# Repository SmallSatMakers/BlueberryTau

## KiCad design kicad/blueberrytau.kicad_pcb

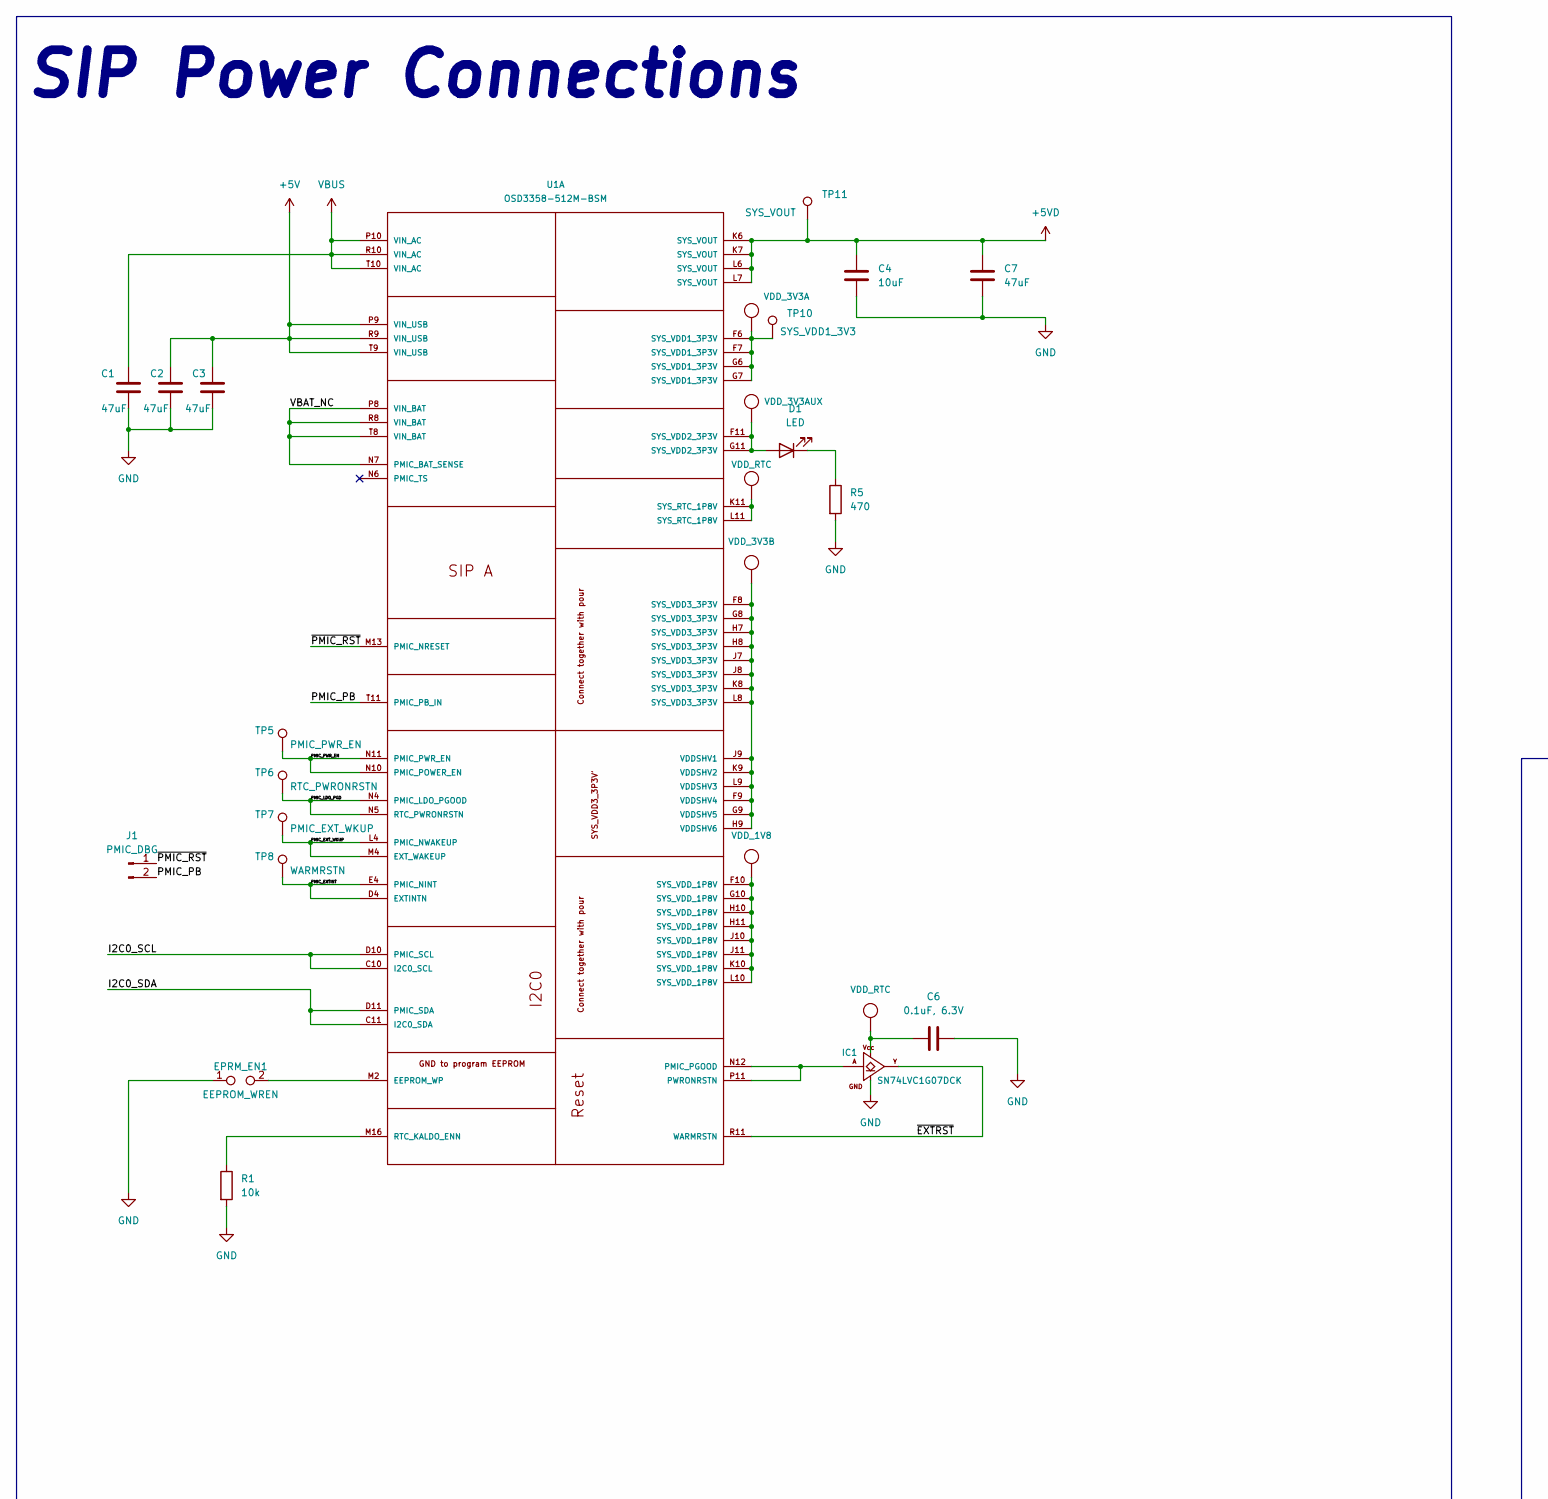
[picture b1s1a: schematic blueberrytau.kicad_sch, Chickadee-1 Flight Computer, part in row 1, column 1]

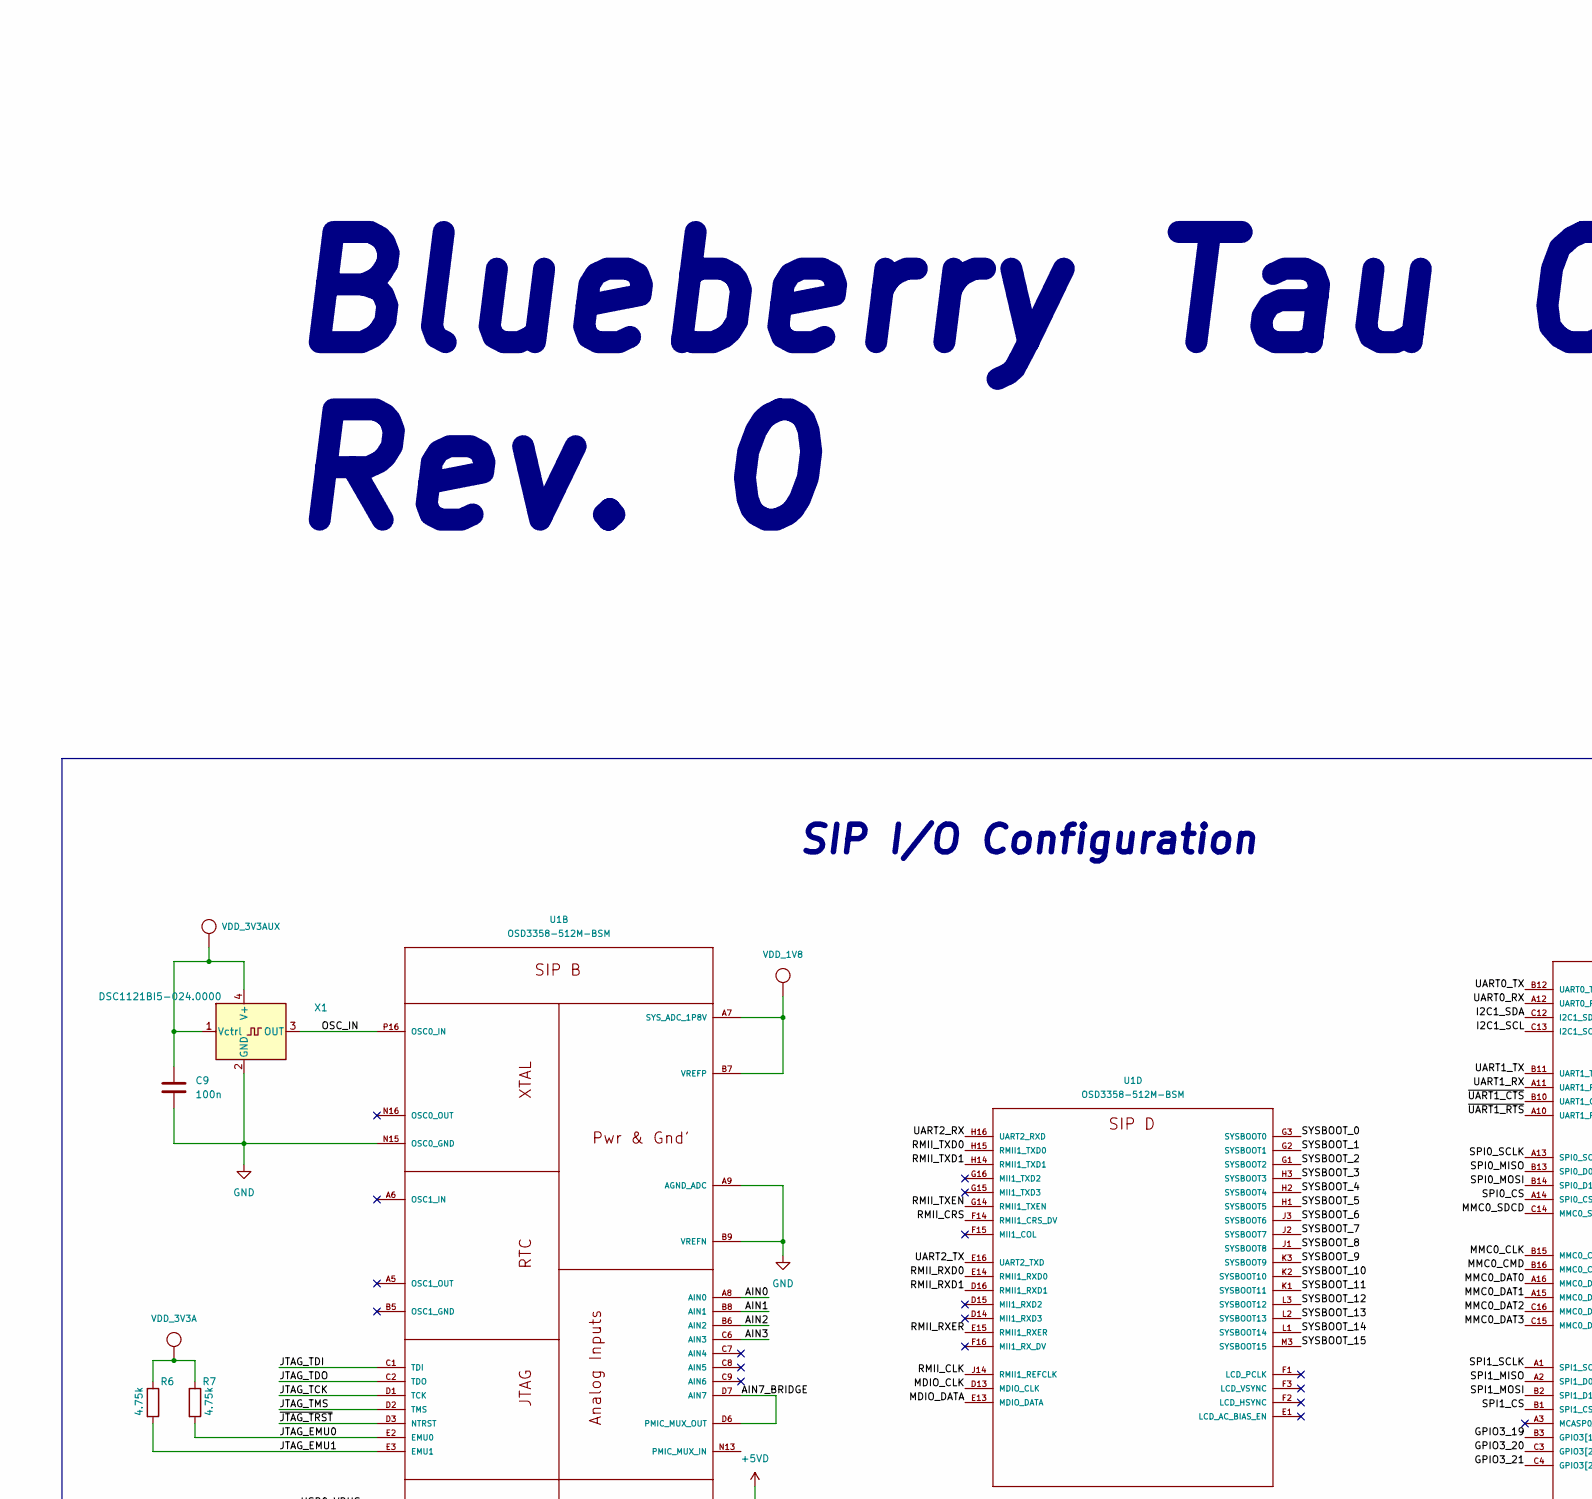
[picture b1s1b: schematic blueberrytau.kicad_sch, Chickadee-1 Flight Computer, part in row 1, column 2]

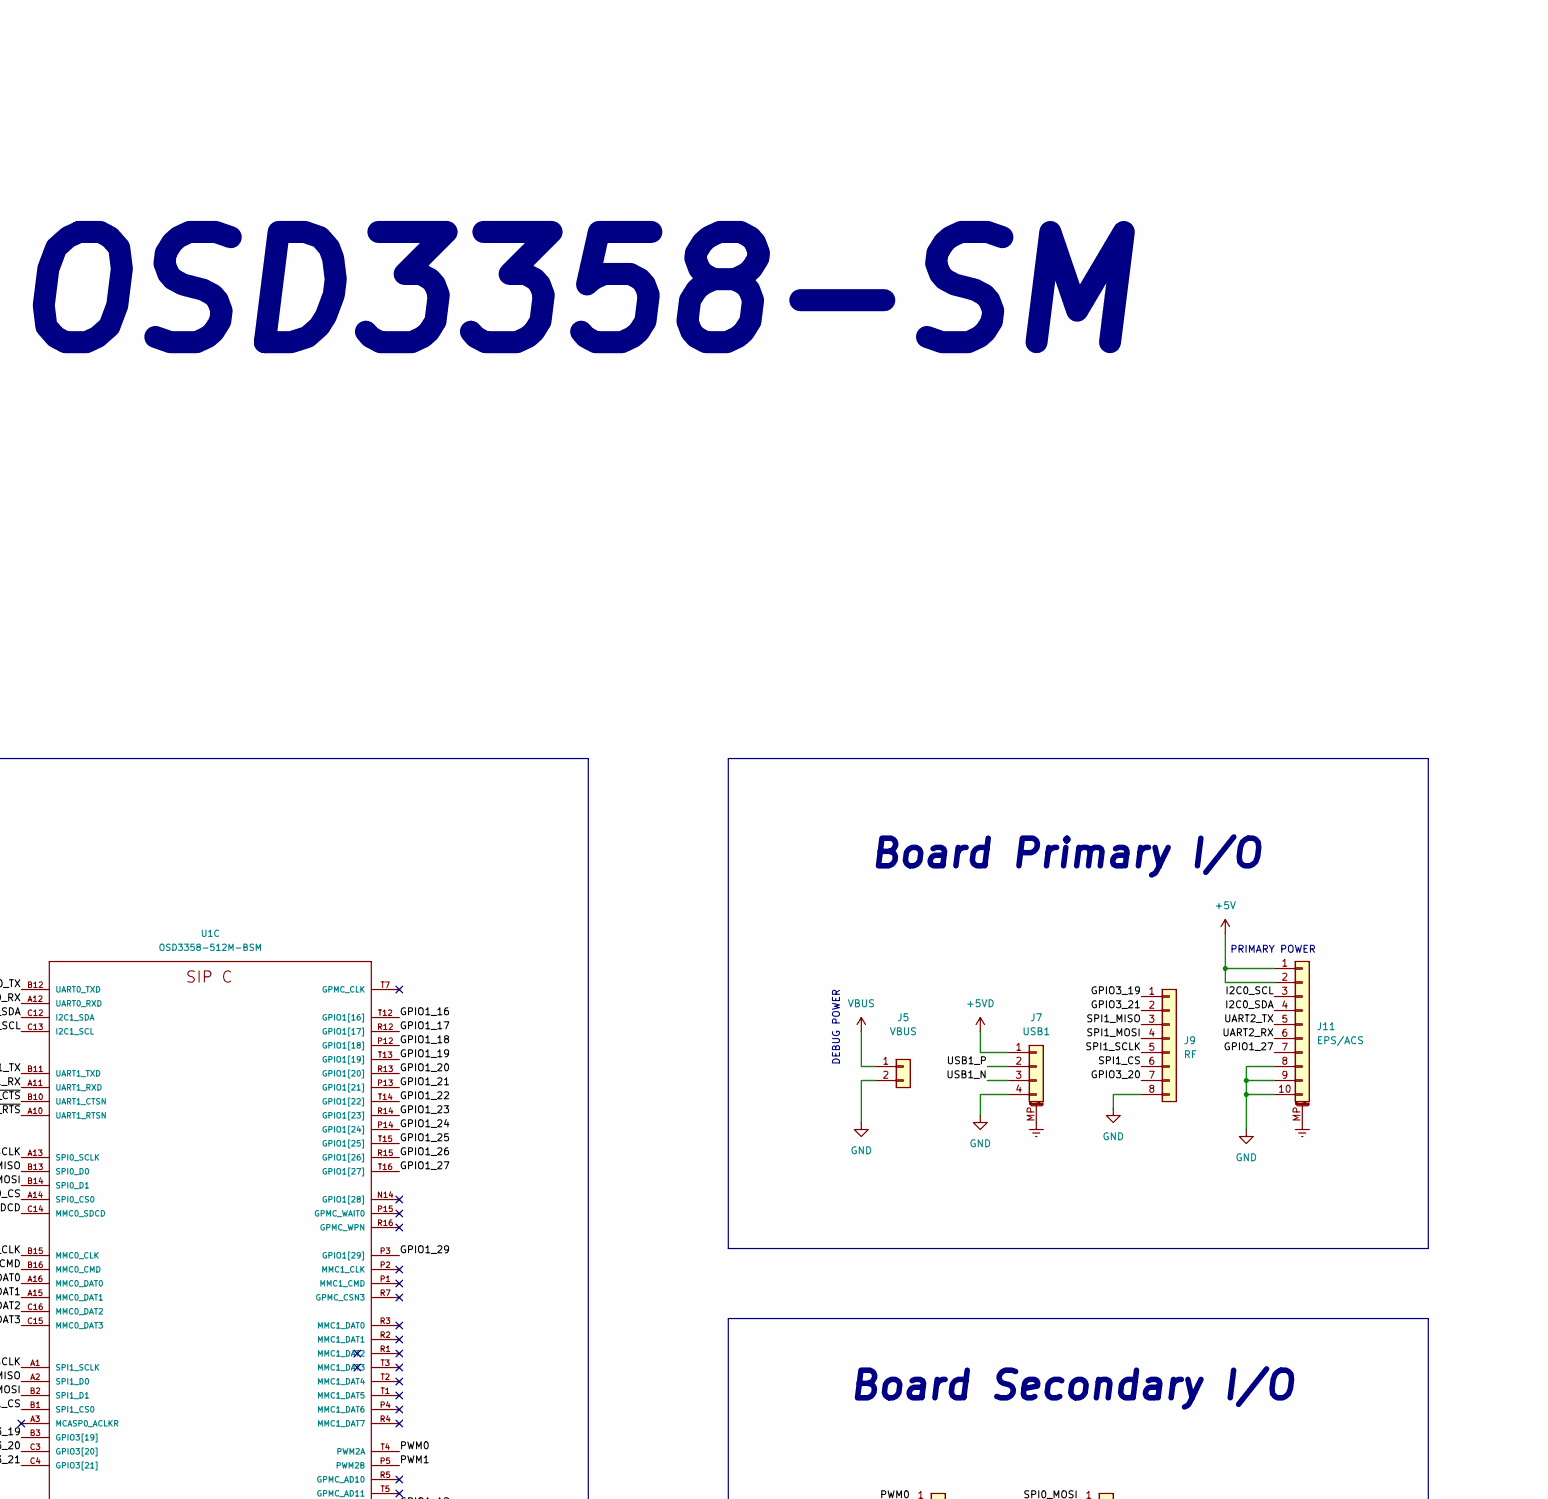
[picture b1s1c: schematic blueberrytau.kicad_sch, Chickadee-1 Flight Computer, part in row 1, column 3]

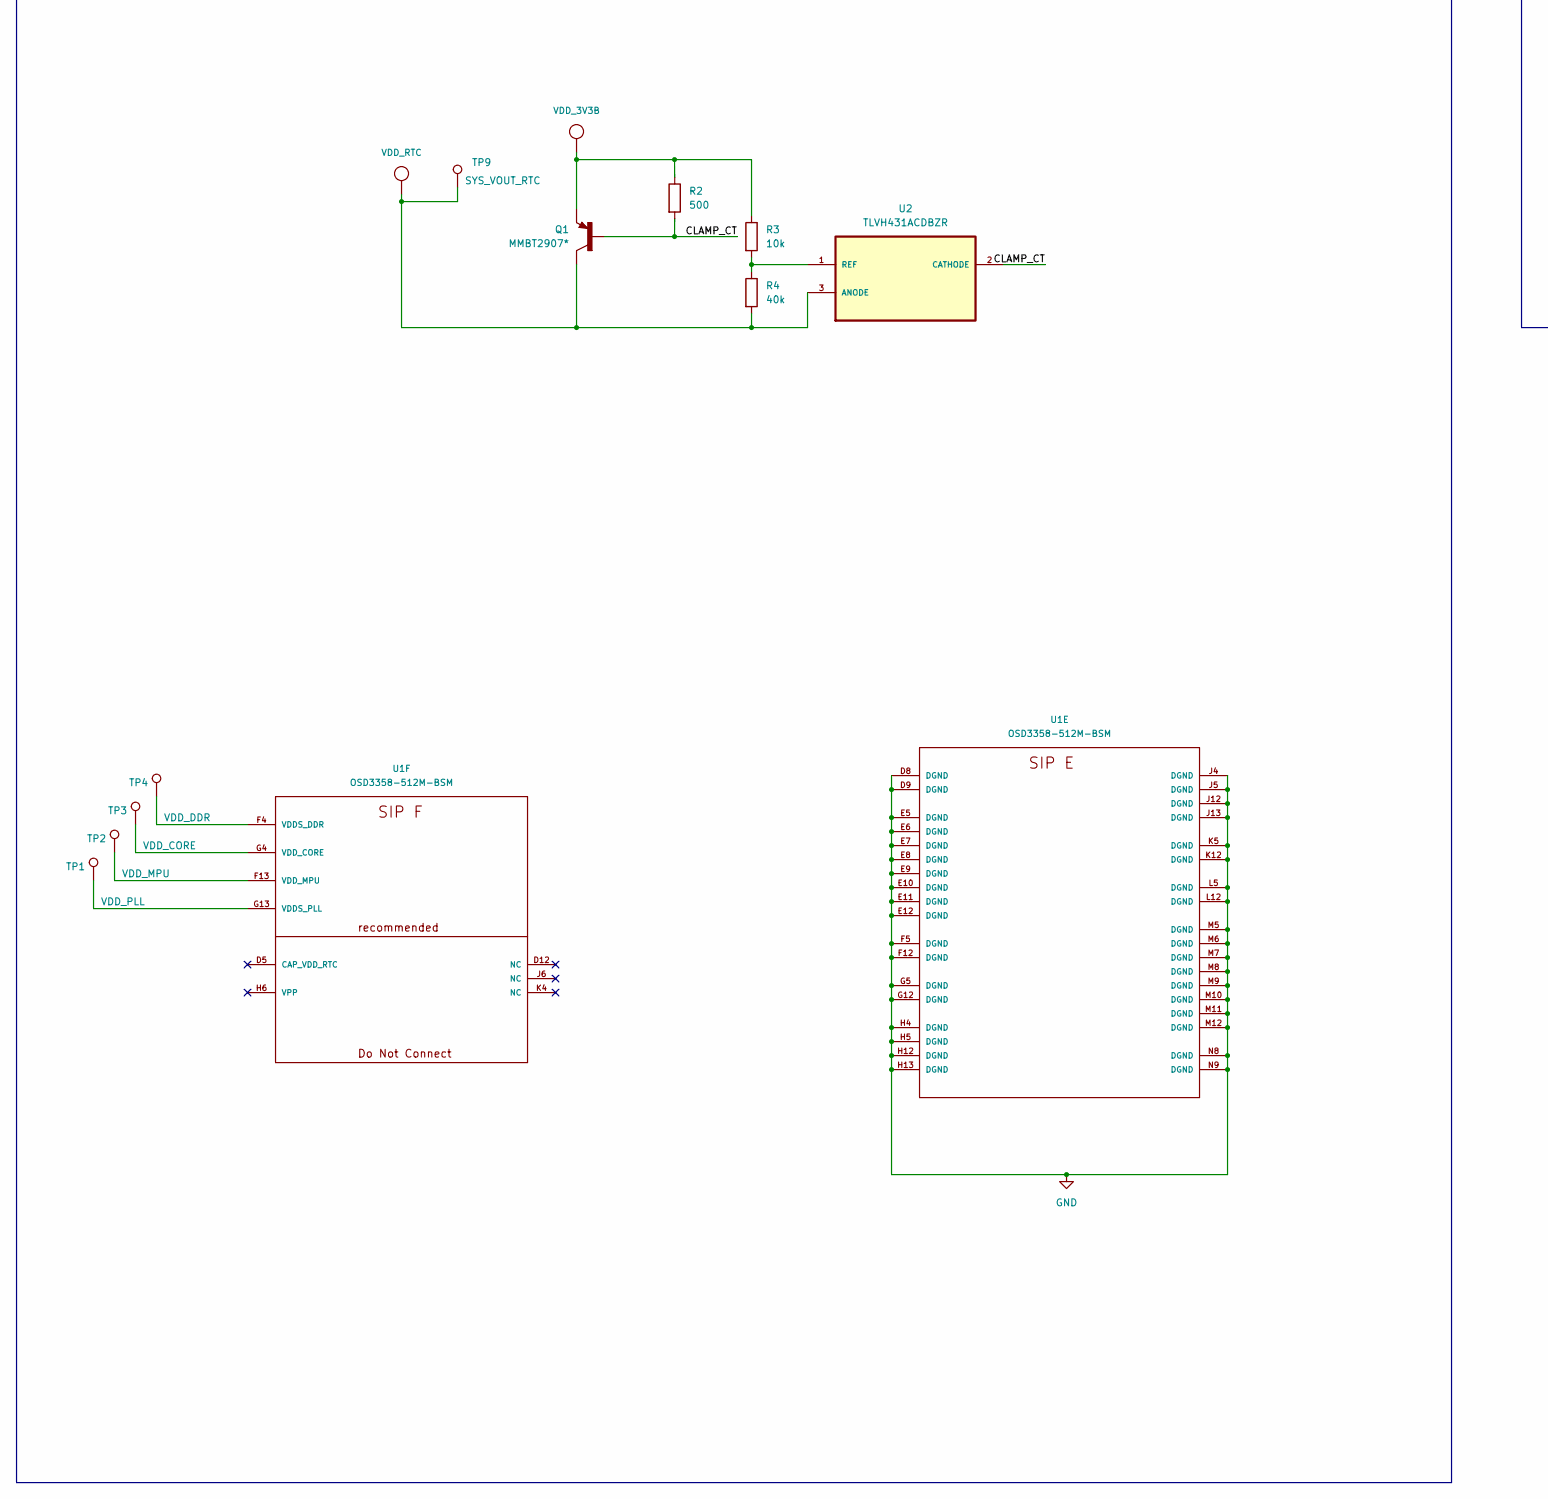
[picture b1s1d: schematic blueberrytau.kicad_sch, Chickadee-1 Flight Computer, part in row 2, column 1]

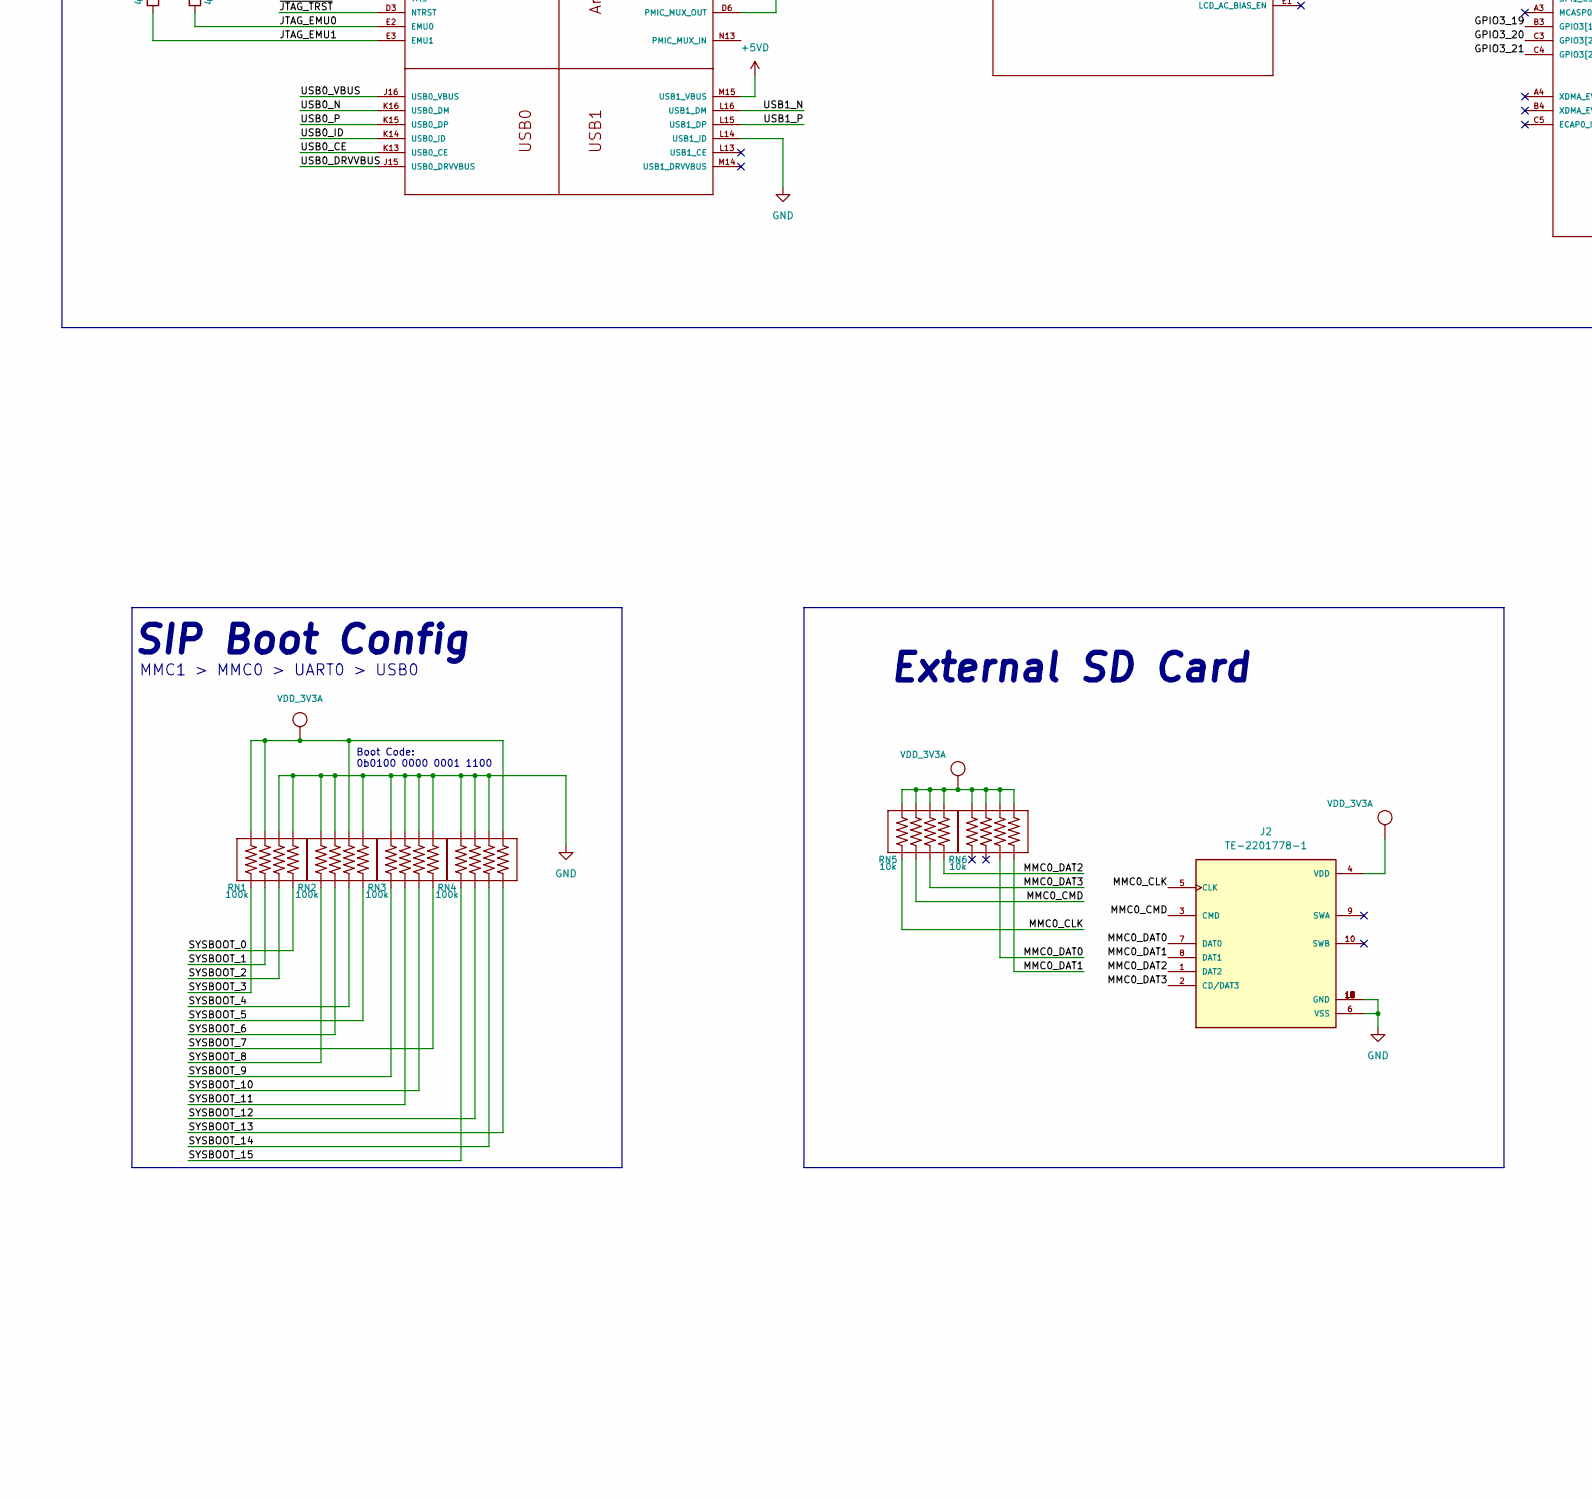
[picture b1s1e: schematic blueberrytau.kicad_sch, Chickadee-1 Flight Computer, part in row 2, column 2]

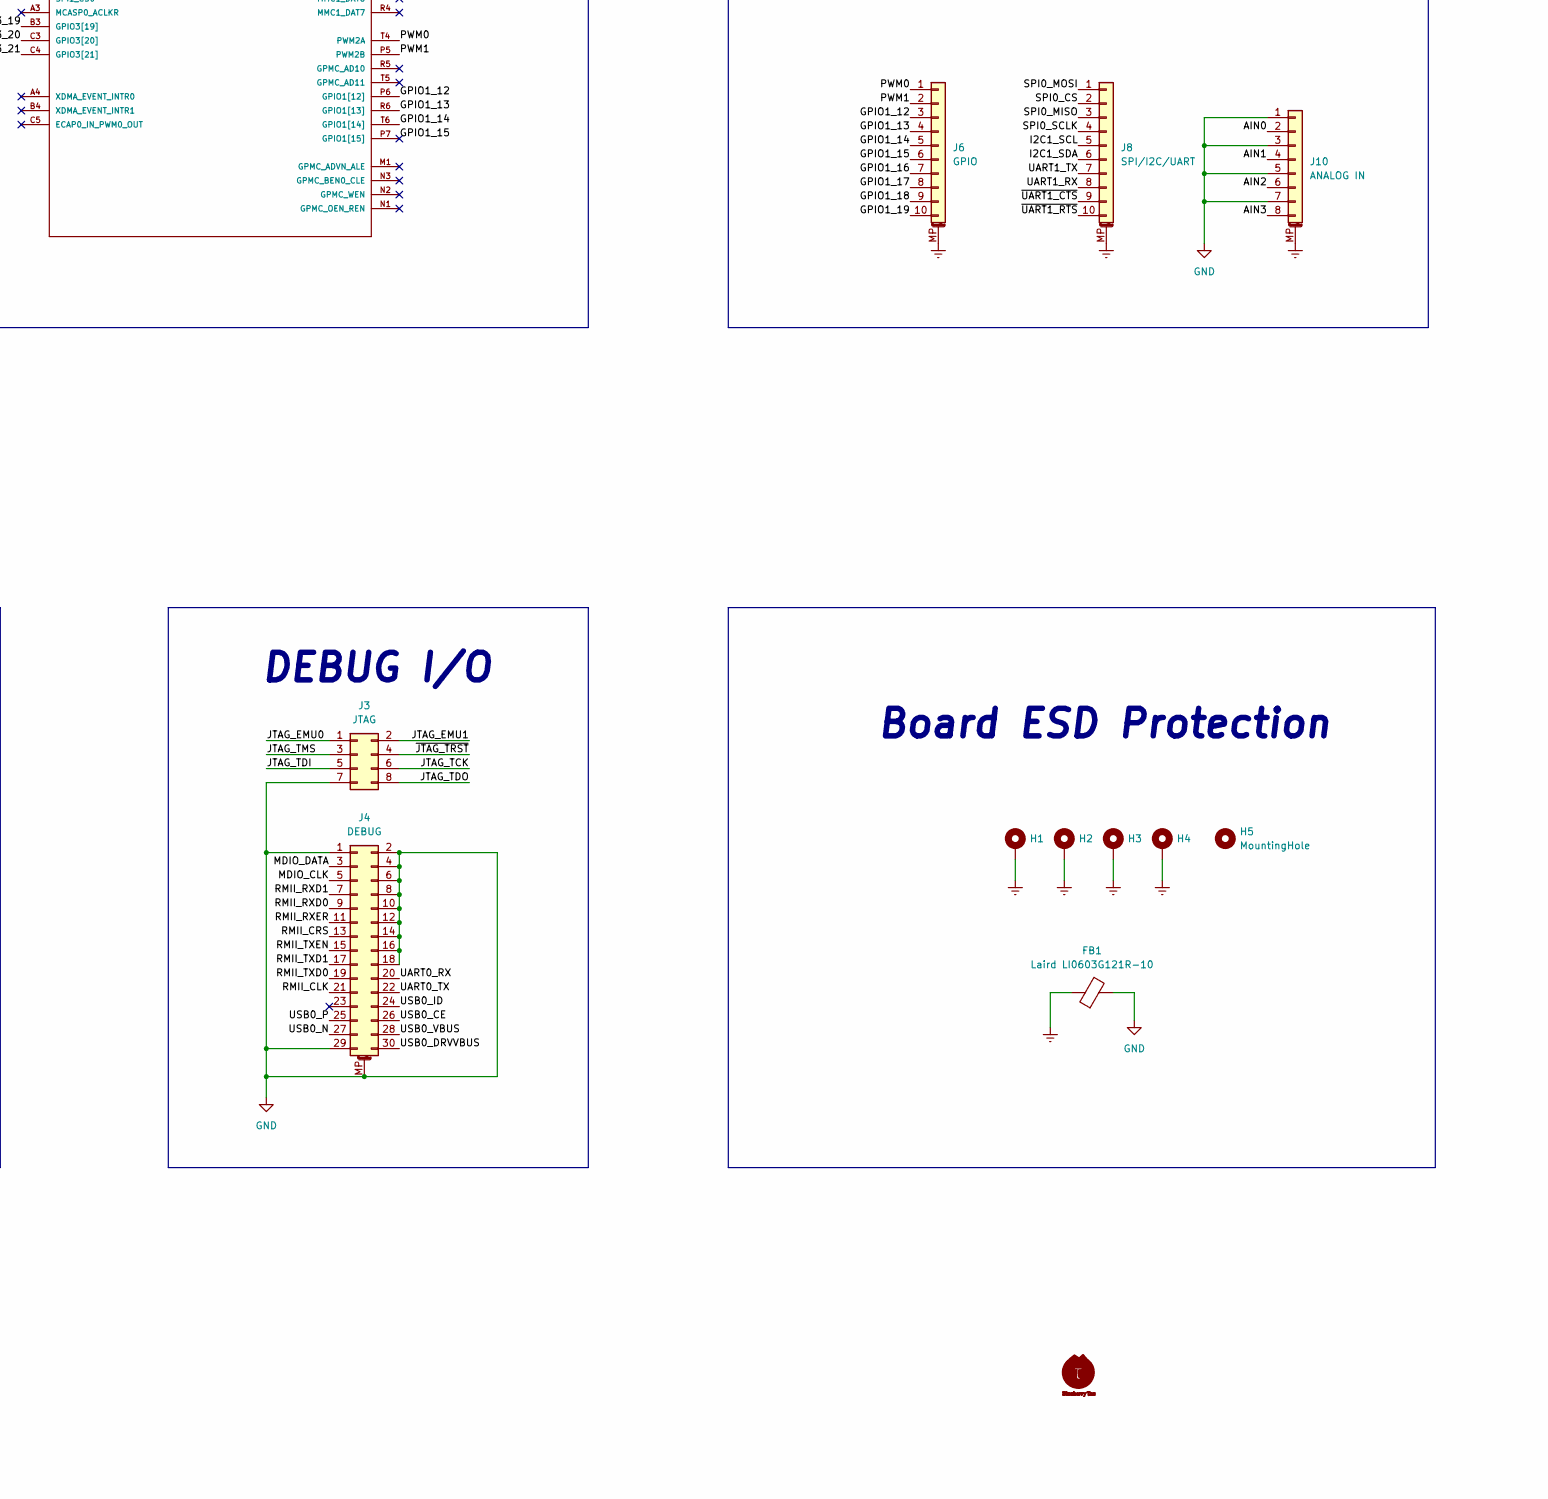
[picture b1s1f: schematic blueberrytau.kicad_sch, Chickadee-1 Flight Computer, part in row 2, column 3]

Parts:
C1, C2, C3, C7: 47uF; C_0805_2012Metric
C4: 10uF; C_0805_2012Metric
C6: 0.1uF, 6.3V; C_0402_1005Metric
C9: 100n; C_0402_1005Metric
D1: LED; LED_0402_1005Metric
EPRM_EN1: EEPROM_WREN; TestPoint_2Pads_Pitch2.54mm_Drill0.8mm
FB1: Laird LI0603G121R-10; R_0603_1608Metric
H1, H2, H3, H4: MountingHole_Pad; MountingHole_2.2mm_M2_Pad_Via
H5: MountingHole; MountingHole_2.1mm
IC1: SN74LVC1G07DCK; SC70(TI-DCK)
J1: PMIC_DBG; PinHeader_1x02_P2.00mm_Vertical
J2: TE-2201778-1; TE_2201778-1
J3: JTAG; MLE-104-01-G-DV
J4: DEBUG; PANASONIC_AXT630124
J5: VBUS; PinHeader_1x02_P2.54mm_Vertical
J6: GPIO; Molex_PicoBlade_53398-1071_1x10-1MP_P1.25mm_Vertical
J7: USB1; Molex_PicoBlade_53398-0471_1x04-1MP_P1.25mm_Vertical
J8: SPI/I2C/UART; Molex_PicoBlade_53398-1071_1x10-1MP_P1.25mm_Vertical
J9: RF; PinHeader_2x04_P1.00mm_Vertical
J10: ANALOG IN; Molex_PicoBlade_53398-0871_1x08-1MP_P1.25mm_Vertical
J11: EPS/ACS; Molex_PicoBlade_53398-1071_1x10-1MP_P1.25mm_Vertical
Q1: MMBT2907*; SOT-723
R1: 10k; R_0201_0603Metric
R2: 500; R_0805_2012Metric
R3: 10k; R_0402_1005Metric
R4: 40k; R_0402_1005Metric
R5: 470; R_0402_1005Metric
R6, R7: 4.75k; R_0201_0603Metric
RN1, RN2, RN3, RN4: 100k; RN0804
RN5, RN6: 10k; RN0804
TP1: VDD_PLL; TestPoint_Pad_D1.0mm
TP2: VDD_MPU; TestPoint_Pad_D1.0mm
TP3: VDD_CORE; TestPoint_Pad_D1.0mm
TP4: VDD_DDR; TestPoint_Pad_D1.0mm
TP5: PMIC_PWR_EN; TestPoint_Pad_D1.0mm
TP6: RTC_PWRONRSTN; TestPoint_Pad_D1.0mm
TP7: PMIC_EXT_WKUP; TestPoint_Pad_D1.0mm
TP8: WARMRSTN; TestPoint_Pad_D1.0mm
TP9: SYS_VOUT_RTC; TestPoint_Pad_D1.0mm
TP10: SYS_VDD1_3V3; TestPoint_Pad_D1.0mm
TP11: SYS_VOUT; TestPoint_Pad_D1.0mm
U1: OSD3358-512M-BSM; OSD335X-BGA-256
U2: TLVH431ACDBZR; SOT-23; MPN TLVH431ACDBZR
X1: DSC1121BI5-024.0000; Oscillator_SMD_Fordahl_DFAS15-4Pin_5.0x3.2mm

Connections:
+5V: C2.1, C3.1, J11.1, J11.2, U1.P9 (VIN_USB), U1.R9 (VIN_USB), U1.T9 (VIN_USB)
+5VD: C4.1, C7.1, J7.1, TP11.1, U1.K6 (SYS_VOUT), U1.K7 (SYS_VOUT), U1.L6 (SYS_VOUT), U1.L7 (SYS_VOUT), U1.M15 (USB1_VBUS)
/AIN0: J10.2, U1.A8 (AIN0)
/AIN1: J10.4, U1.B8 (AIN1)
/AIN2: J10.6, U1.B6 (AIN2)
/AIN3: J10.8, U1.C6 (AIN3)
/AIN7_BRIDGE: U1.D6 (PMIC_MUX_OUT), U1.D7 (AIN7)
/CLAMP_CT: Q1.1 (B), R2.2, U2.2 (CATHODE)
/GPIO1_12: J6.3, U1.P6 (GPIO1[12])
/GPIO1_13: J6.4, U1.R6 (GPIO1[13])
/GPIO1_14: J6.5, U1.T6 (GPIO1[14])
/GPIO1_15: J6.6, U1.P7 (GPIO1[15])
/GPIO1_16: J6.7, U1.T12 (GPIO1[16])
/GPIO1_17: J6.8, U1.R12 (GPIO1[17])
/GPIO1_18: J6.9, U1.P12 (GPIO1[18])
/GPIO1_19: J6.10, U1.T13 (GPIO1[19])
/GPIO1_20: U1.R13 (GPIO1[20])
/GPIO1_21: U1.P13 (GPIO1[21])
/GPIO1_22: U1.T14 (GPIO1[22])
/GPIO1_23: U1.R14 (GPIO1[23])
/GPIO1_24: U1.P14 (GPIO1[24])
/GPIO1_25: U1.T15 (GPIO1[25])
/GPIO1_26: U1.R15 (GPIO1[26])
/GPIO1_27: J11.7, U1.T16 (GPIO1[27])
/GPIO1_29: U1.P3 (GPIO1[29])
/GPIO3_19: J9.1, U1.B3 (GPIO3[19])
/GPIO3_20: J9.7, U1.C3 (GPIO3[20])
/GPIO3_21: J9.2, U1.C4 (GPIO3[21])
/I2C0_SCL: J11.3, U1.C10 (I2C0_SCL), U1.D10 (PMIC_SCL)
/I2C0_SDA: J11.4, U1.C11 (I2C0_SDA), U1.D11 (PMIC_SDA)
/I2C1_SCL: J8.5, U1.C13 (I2C1_SCL)
/I2C1_SDA: J8.6, U1.C12 (I2C1_SDA)
/JTAG_EMU0: J3.1, R7.2, U1.E2 (EMU0)
/JTAG_EMU1: J3.2, R6.2, U1.E3 (EMU1)
/JTAG_TCK: J3.6, U1.D1 (TCK)
/JTAG_TDI: J3.5, U1.C1 (TDI)
/JTAG_TDO: J3.8, U1.C2 (TDO)
/JTAG_TMS: J3.3, U1.D2 (TMS)
/MDIO_CLK: J4.5, U1.D13 (MDIO_CLK)
/MDIO_DATA: J4.3, U1.E13 (MDIO_DATA)
/MMC0_CLK: J2.5 (CLK), RN5.1, U1.B15 (MMC0_CLK)
/MMC0_CMD: J2.3 (CMD), RN5.2, U1.B16 (MMC0_CMD)
/MMC0_DAT0: J2.7 (DAT0), RN6.3, U1.A16 (MMC0_DAT0)
/MMC0_DAT1: J2.8 (DAT1), RN6.4, U1.A15 (MMC0_DAT1)
/MMC0_DAT2: J2.1 (DAT2), RN5.4, U1.C16 (MMC0_DAT2)
/MMC0_DAT3: J2.2 (CD/DAT3), RN5.3, U1.C15 (MMC0_DAT3)
/MMC0_SDCD: U1.C14 (MMC0_SDCD)
/OSC_IN: U1.P16 (OSC0_IN), X1.3 (OUT)
/PMIC_EXTINT: TP8.1, U1.D4 (EXTINTN), U1.E4 (PMIC_NINT)
/PMIC_EXT_WKUP: TP7.1, U1.L4 (PMIC_NWAKEUP), U1.M4 (EXT_WAKEUP)
/PMIC_LDO_PGD: TP6.1, U1.N4 (PMIC_LDO_PGOOD), U1.N5 (RTC_PWRONRSTN)
/PMIC_PB: J1.2, U1.T11 (PMIC_PB_IN)
/PMIC_PWR_EN: TP5.1, U1.N10 (PMIC_POWER_EN), U1.N11 (PMIC_PWR_EN)
/PWM0: J6.1, U1.T4 (PWM2A)
/PWM1: J6.2, U1.P5 (PWM2B)
/RMII_CLK: J4.21, U1.J14 (RMII1_REFCLK)
/RMII_CRS: J4.13, U1.F14 (RMII1_CRS_DV)
/RMII_RXD0: J4.9, U1.E14 (RMII1_RXD0)
/RMII_RXD1: J4.7, U1.D16 (RMII1_RXD1)
/RMII_RXER: J4.11, U1.E15 (RMII1_RXER)
/RMII_TXD0: J4.19, U1.H15 (RMII1_TXD0)
/RMII_TXD1: J4.17, U1.H14 (RMII1_TXD1)
/RMII_TXEN: J4.15, U1.G14 (RMII1_TXEN)
/SPI0_CS: J8.2, U1.A14 (SPI0_CS0)
/SPI0_MISO: J8.3, U1.B13 (SPI0_D0)
/SPI0_MOSI: J8.1, U1.B14 (SPI0_D1)
/SPI0_SCLK: J8.4, U1.A13 (SPI0_SCLK)
/SPI1_CS: J9.6, U1.B1 (SPI1_CS0)
/SPI1_MISO: J9.3, U1.A2 (SPI1_D0)
/SPI1_MOSI: J9.4, U1.B2 (SPI1_D1)
/SPI1_SCLK: J9.5, U1.A1 (SPI1_SCLK)
/SYSBOOT_0: RN1.4, U1.G3 (SYSBOOT0)
/SYSBOOT_1: RN1.2, U1.G2 (SYSBOOT1)
/SYSBOOT_2: RN1.3, U1.G1 (SYSBOOT2)
/SYSBOOT_3: RN1.1, U1.H3 (SYSBOOT3)
/SYSBOOT_4: RN2.3, U1.H2 (SYSBOOT4)
/SYSBOOT_5: RN2.4, U1.H1 (SYSBOOT5)
/SYSBOOT_6: RN2.2, U1.J3 (SYSBOOT6)
/SYSBOOT_7: RN3.4, U1.J2 (SYSBOOT7)
/SYSBOOT_8: RN2.1, U1.J1 (SYSBOOT8)
/SYSBOOT_9: RN3.1, U1.K3 (SYSBOOT9)
/SYSBOOT_10: RN3.3, U1.K2 (SYSBOOT10)
/SYSBOOT_11: RN3.2, U1.K1 (SYSBOOT11)
/SYSBOOT_12: RN4.2, U1.L3 (SYSBOOT12)
/SYSBOOT_13: RN4.4, U1.L2 (SYSBOOT13)
/SYSBOOT_14: RN4.3, U1.L1 (SYSBOOT14)
/SYSBOOT_15: RN4.1, U1.M3 (SYSBOOT15)
/UART0_RX: J4.20, U1.A12 (UART0_RXD)
/UART0_TX: J4.22, U1.B12 (UART0_TXD)
/UART1_RX: J8.8, U1.A11 (UART1_RXD)
/UART1_TX: J8.7, U1.B11 (UART1_TXD)
/UART2_RX: J11.6, U1.H16 (UART2_RXD)
/UART2_TX: J11.5, U1.E16 (UART2_TXD)
/USB0_CE: J4.26, U1.K13 (USB0_CE)
/USB0_DRVVBUS: J4.30, U1.J15 (USB0_DRVVBUS)
/USB0_ID: J4.24, U1.K14 (USB0_ID)
/USB0_N: J4.27, U1.K16 (USB0_DM)
/USB0_P: J4.25, U1.K15 (USB0_DP)
/USB0_VBUS: J4.28, U1.J16 (USB0_VBUS)
/USB1_N: J7.3, U1.L16 (USB1_DM)
/USB1_P: J7.2, U1.L15 (USB1_DP)
/VBAT_NC: U1.N7 (PMIC_BAT_SENSE), U1.P8 (VIN_BAT), U1.R8 (VIN_BAT), U1.T8 (VIN_BAT)
/~EXTRST: IC1.4 (Y), U1.R11 (WARMRSTN)
/~JTAG_TRST: J3.4, U1.D3 (NTRST)
/~PMIC_RST: J1.1, U1.M13 (PMIC_NRESET)
/~UART1_CTS: J8.9, U1.B10 (UART1_CTSN)
/~UART1_RTS: J8.10, U1.A10 (UART1_RTSN)
Earth: FB1.1, H1.1, H2.1, H3.1, H4.1, J6.MP (MountPin), J7.MP (MountPin), J8.MP (MountPin), J10.MP (MountPin), J11.MP (MountPin)
GND: C1.2, C2.2, C3.2, C4.2, C6.2, C7.2, C9.2, EPRM_EN1.1, FB1.2, IC1.3 (GND), J2.6 (VSS), J2.11 (GND), J2.12 (GND), J2.13 (GND), J2.14 (GND), J2.15 (GND), J2.16 (GND), J3.7, J4.1, J4.2, J4.4, J4.6, J4.8, J4.10, J4.12, J4.14, J4.16, J4.18, J4.29, J4.MP (MountPin), J5.2, J7.4, J9.8, J10.1, J10.3, J10.5, J10.7, J11.8, J11.9, J11.10, R1.2, R5.2, RN1.5, RN1.6, RN2.5, RN2.7, RN2.8, RN3.5, RN3.6, RN3.7, RN3.8, RN4.6, RN4.7, RN4.8, U1.A9 (AGND_ADC), U1.B9 (VREFN), U1.D8 (DGND), U1.D9 (DGND), U1.E5 (DGND), U1.E6 (DGND), U1.E7 (DGND), U1.E8 (DGND), U1.E9 (DGND), U1.E10 (DGND), U1.E11 (DGND), U1.E12 (DGND), U1.F5 (DGND), U1.F12 (DGND), U1.G5 (DGND), U1.G12 (DGND), U1.H4 (DGND), U1.H5 (DGND), U1.H12 (DGND), U1.H13 (DGND), U1.J4 (DGND), U1.J5 (DGND), U1.J12 (DGND), U1.J13 (DGND), U1.K5 (DGND), U1.K12 (DGND), U1.L5 (DGND), U1.L12 (DGND), U1.L14 (USB1_ID), U1.M5 (DGND), U1.M6 (DGND), U1.M7 (DGND), U1.M8 (DGND), U1.M9 (DGND), U1.M10 (DGND), U1.M11 (DGND), U1.M12 (DGND), U1.N8 (DGND), U1.N9 (DGND), U1.N15 (OSC0_GND), X1.2 (GND)
unnamed: D1.1 (K), R5.1
unnamed: EPRM_EN1.2, U1.M2 (EEPROM_WP)
unnamed: IC1.2 (A), U1.N12 (PMIC_PGOOD), U1.P11 (PWRONRSTN)
unnamed: R1.1, U1.M16 (RTC_KALDO_ENN)
unnamed: R3.2, R4.1, U2.1 (REF)
unnamed: TP1.1, U1.G13 (VDDS_PLL)
unnamed: TP2.1, U1.F13 (VDD_MPU)
unnamed: TP3.1, U1.G4 (VDD_CORE)
unnamed: TP4.1, U1.F4 (VDDS_DDR)
VBUS: C1.1, J5.1, U1.P10 (VIN_AC), U1.R10 (VIN_AC), U1.T10 (VIN_AC)
VDD_1V8: U1.A7 (SYS_ADC_1P8V), U1.B7 (VREFP), U1.F10 (SYS_VDD_1P8V), U1.G10 (SYS_VDD_1P8V), U1.H10 (SYS_VDD_1P8V), U1.H11 (SYS_VDD_1P8V), U1.J10 (SYS_VDD_1P8V), U1.J11 (SYS_VDD_1P8V), U1.K10 (SYS_VDD_1P8V), U1.L10 (SYS_VDD_1P8V)
VDD_3V3A: J2.4 (VDD), R6.1, R7.1, RN1.7, RN1.8, RN2.6, RN4.5, RN5.5, RN5.6, RN5.7, RN5.8, RN6.5, RN6.6, RN6.7, RN6.8, TP10.1, U1.F6 (SYS_VDD1_3P3V), U1.F7 (SYS_VDD1_3P3V), U1.G6 (SYS_VDD1_3P3V), U1.G7 (SYS_VDD1_3P3V)
VDD_3V3AUX: C9.1, D1.2 (A), U1.F11 (SYS_VDD2_3P3V), U1.G11 (SYS_VDD2_3P3V), X1.1 (Vctrl), X1.4 (V+)
VDD_3V3B: Q1.2 (E), R2.1, R3.1, U1.F8 (SYS_VDD3_3P3V), U1.F9 (VDDSHV4), U1.G8 (SYS_VDD3_3P3V), U1.G9 (VDDSHV5), U1.H7 (SYS_VDD3_3P3V), U1.H8 (SYS_VDD3_3P3V), U1.H9 (VDDSHV6), U1.J7 (SYS_VDD3_3P3V), U1.J8 (SYS_VDD3_3P3V), U1.J9 (VDDSHV1), U1.K8 (SYS_VDD3_3P3V), U1.K9 (VDDSHV2), U1.L8 (SYS_VDD3_3P3V), U1.L9 (VDDSHV3)
VDD_RTC: C6.1, IC1.5 (VCC), Q1.3 (C), R4.2, TP9.1, U1.K11 (SYS_RTC_1P8V), U1.L11 (SYS_RTC_1P8V), U2.3 (ANODE)

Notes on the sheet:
DEBUG I/O
DEBUG POWER
SIP Boot Config
Boot Code: 0b0100 0000 0001 1100
Blueberry Tau OSD3358-SM Rev. 0
Board Secondary I/O
MMC1 > MMC0 > UART0 > USB0
SIP I/O Configuration
External SD Card
PRIMARY POWER
Board Primary I/O
Board ESD Protection
SIP Power Connections

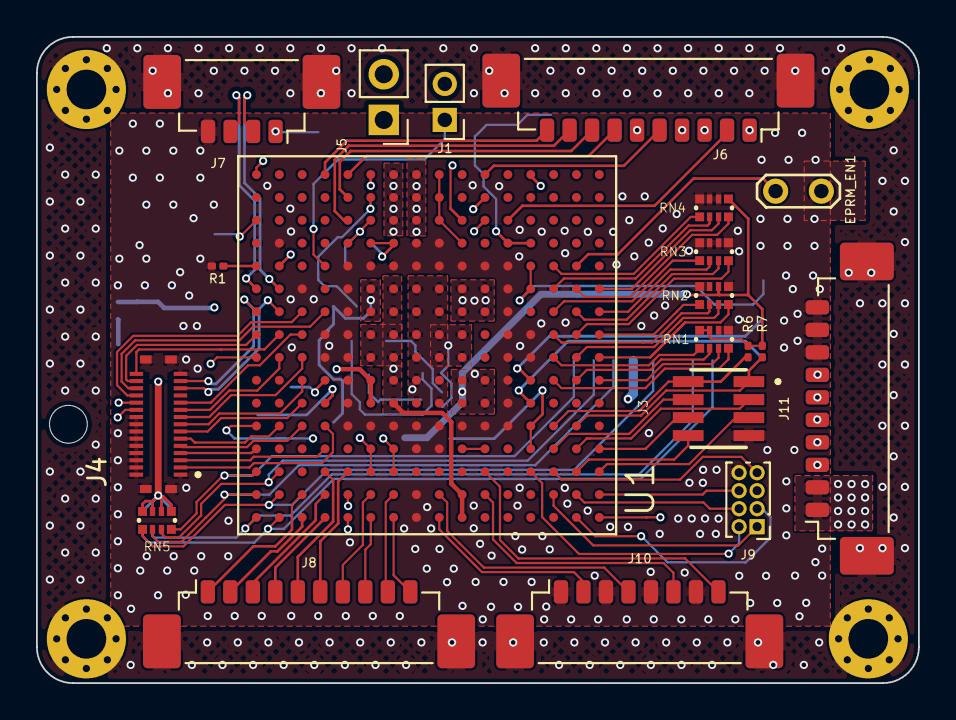
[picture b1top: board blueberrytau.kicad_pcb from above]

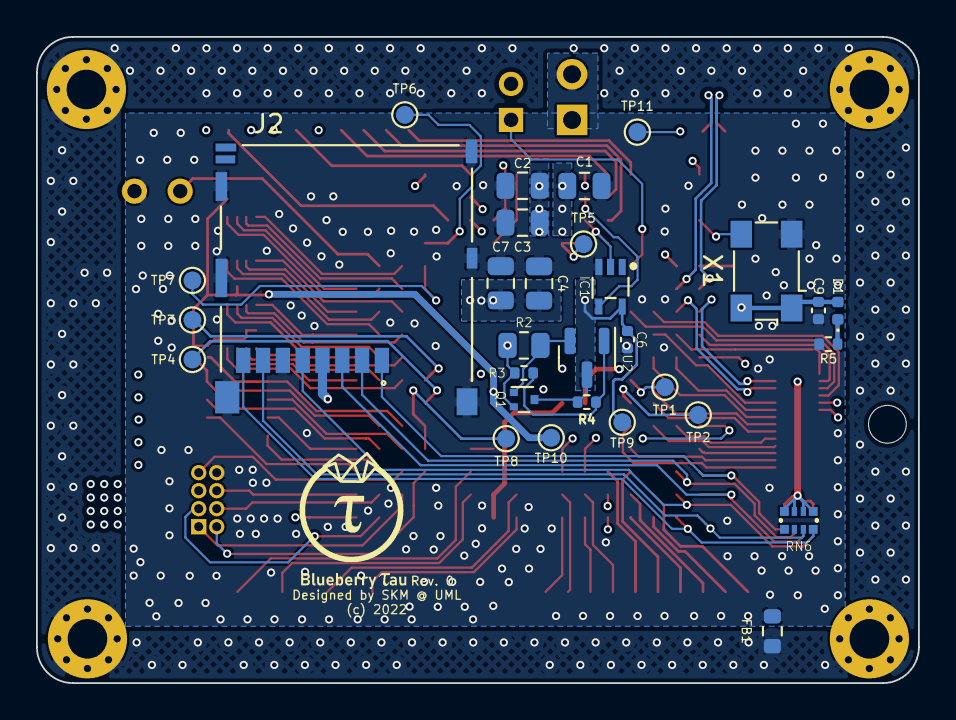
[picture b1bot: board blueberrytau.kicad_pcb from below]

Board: 4 copper layers, 49.0 x 35.9 mm, 55 parts (30 on the bottom side), 115 nets.

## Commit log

2022-03-02 Rev. 0
2022-03-03 Updated microSD slot shield net from earth to ground

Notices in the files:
kicad/blueberrytau.kicad_pcb:
(c) 2022
